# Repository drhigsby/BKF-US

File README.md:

# BKF Unibody Split (BKF-US)

A custom 40% unibody split keyboard PCB designed in KiCad.

## Overview

The BKF Unibody Split is a 4x12 (48-key) unibody split layout — both halves on a single PCB. It uses standard MX switches and is powered by an RP2040 Zero microcontroller.

## Layout

[KLE Preview](https://www.keyboard-layout-editor.com/#/gists/7dcf7c812452a509e0597ead96891f3b)

- 4x12 unibody split
- Standard MX switch footprints
- FR4 plate design included

## Hardware

- **MCU:** RP2040 Zero
- **Switches:** MX compatible
- **Plate:** FR4 (KiCad project included)

## Case

3D printable case files are included in the `case stuff/` directory:

- `bkf unibody split case v4.stl` — current case design
- `bkf unibody split case - extra planar cuts v1.stl` — variant with additional planar cuts
- `bkf unibody split case project.3mf` — OrcaSlicer project file with tuned slicing parameters
- `plate projected geometry only.dxf` — plate geometry for CAD reference
- `pcb test fit v1.stl` — PCB test fit model

## Firmware

VIAL firmware is available in the [drhigsby/vial-qmk](https://github.com/drhigsby/vial-qmk) fork under `keyboards/drhigsby/bkf_us/`.

## Project Structure

```
bkf-unibodysplit - primary pcb/   # Main PCB design
bkf-unibodysplit - plate design/  # FR4 plate design
case stuff/                        # Case STL files and DXFs
```

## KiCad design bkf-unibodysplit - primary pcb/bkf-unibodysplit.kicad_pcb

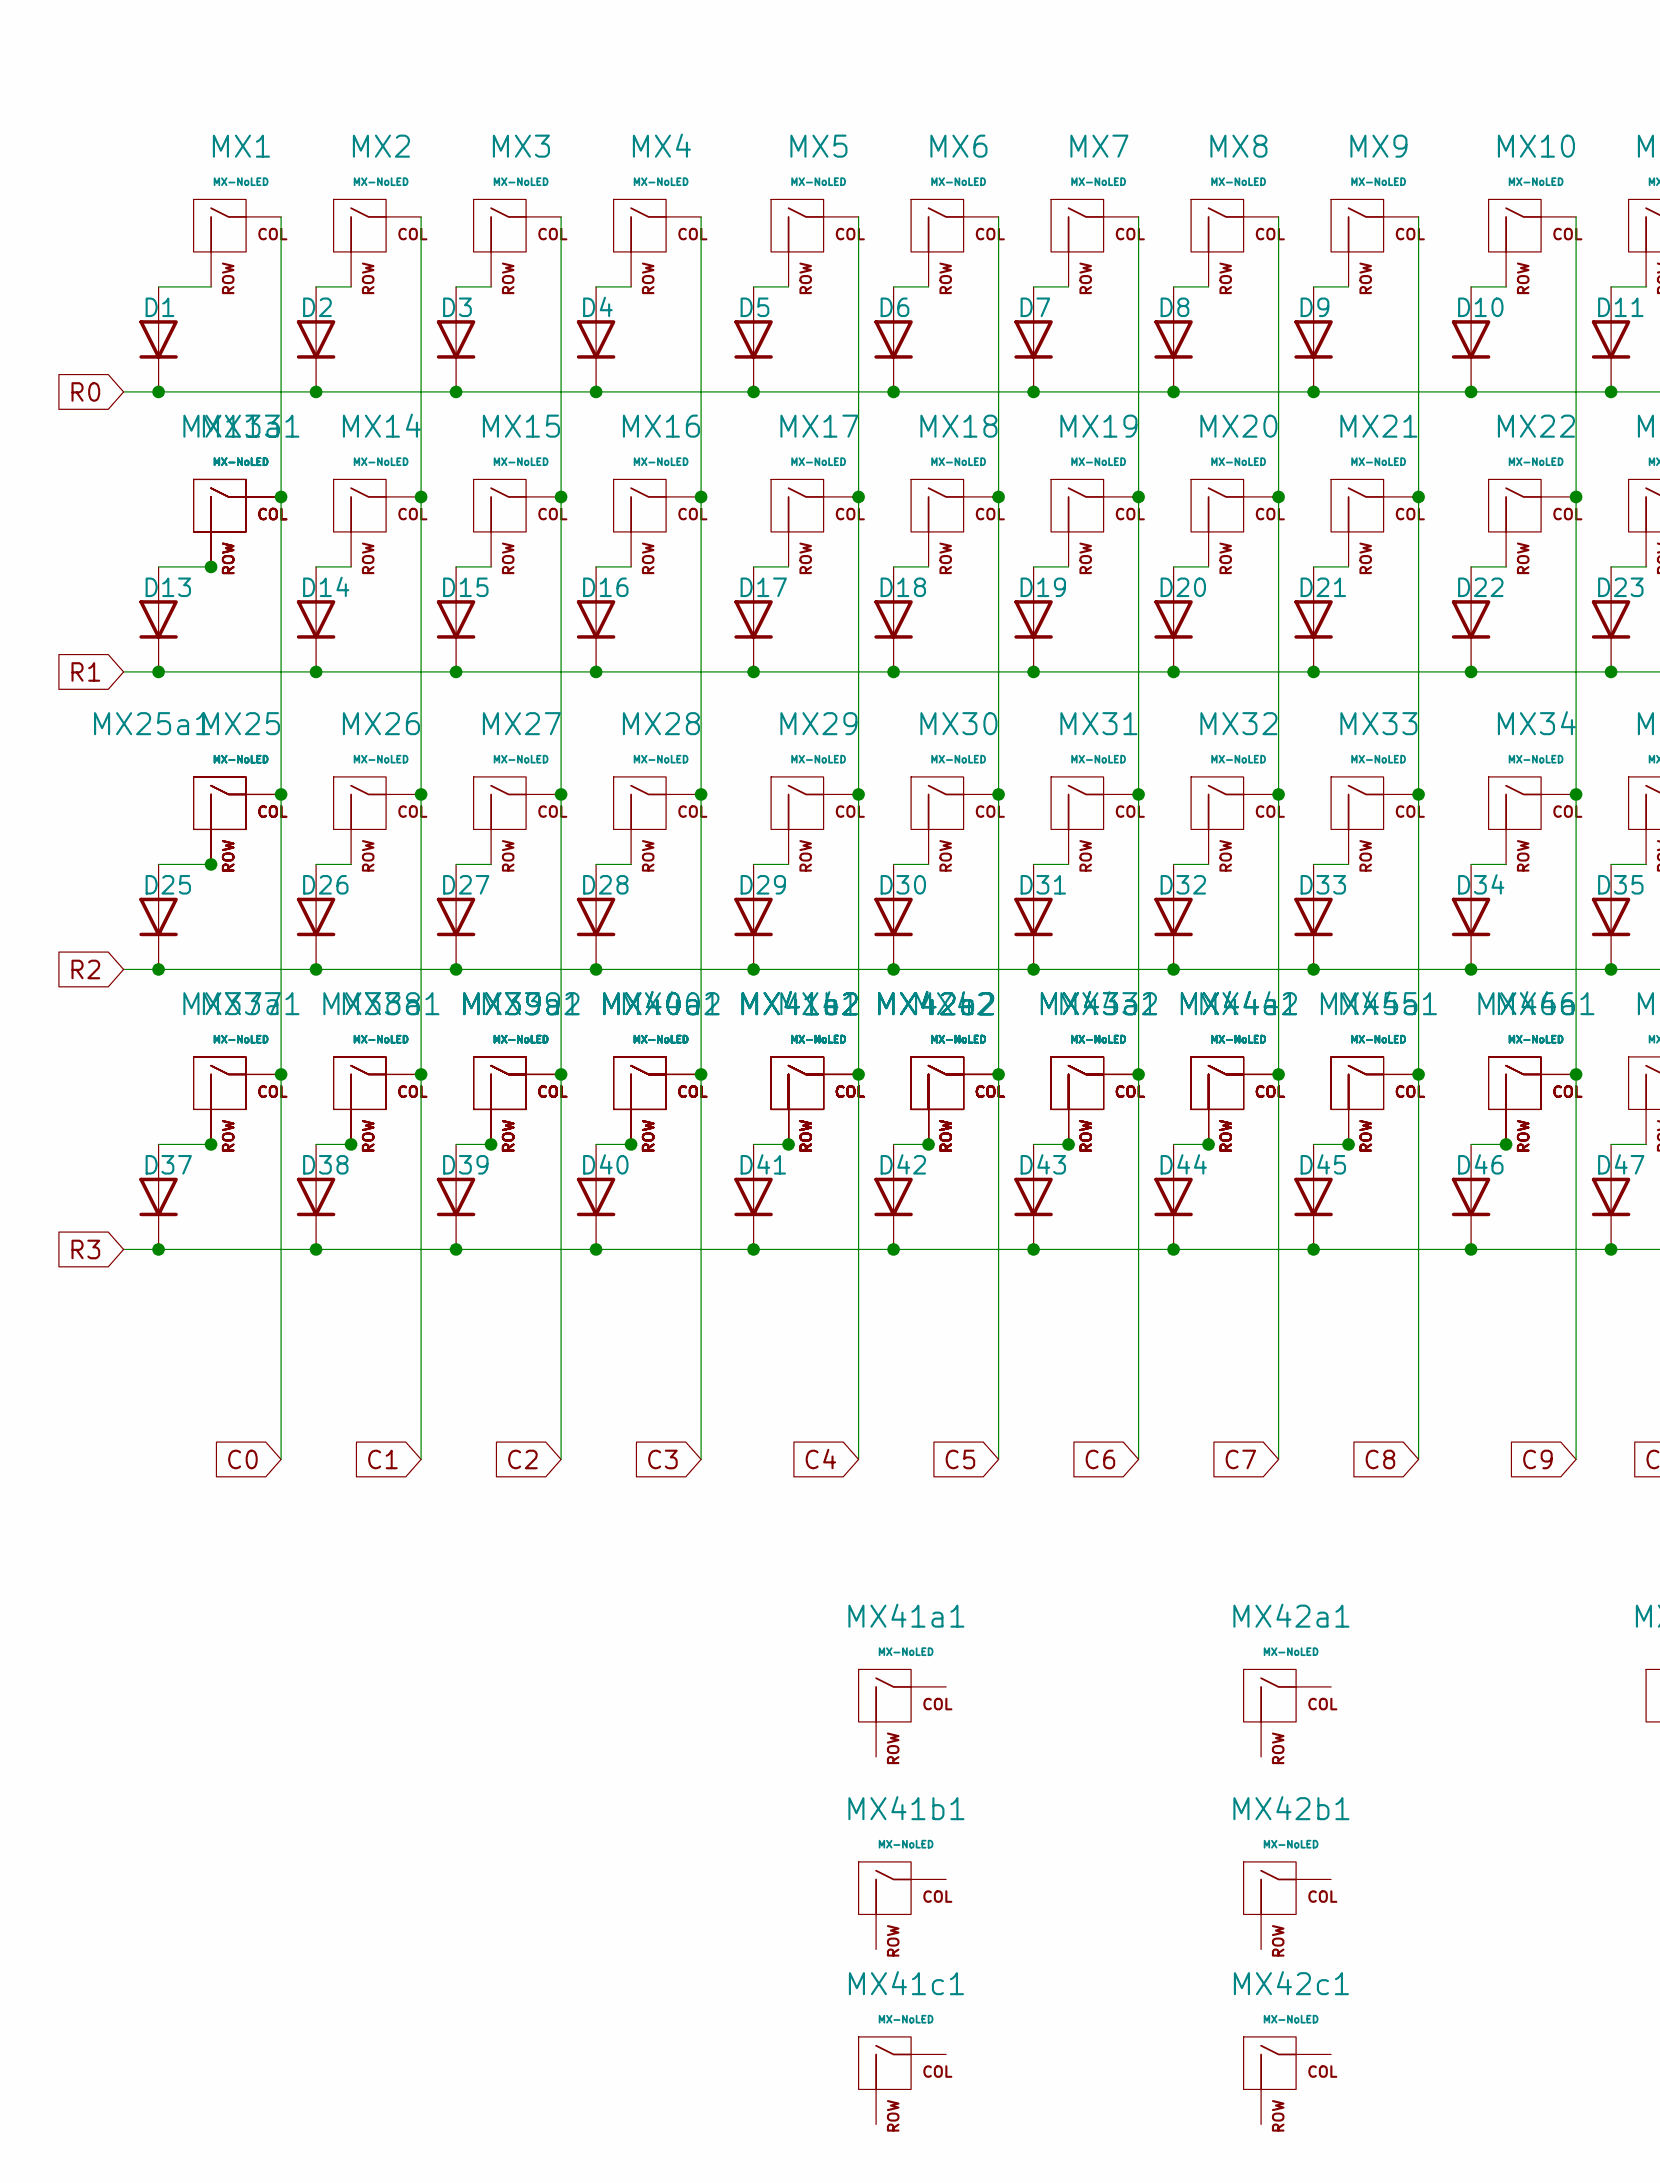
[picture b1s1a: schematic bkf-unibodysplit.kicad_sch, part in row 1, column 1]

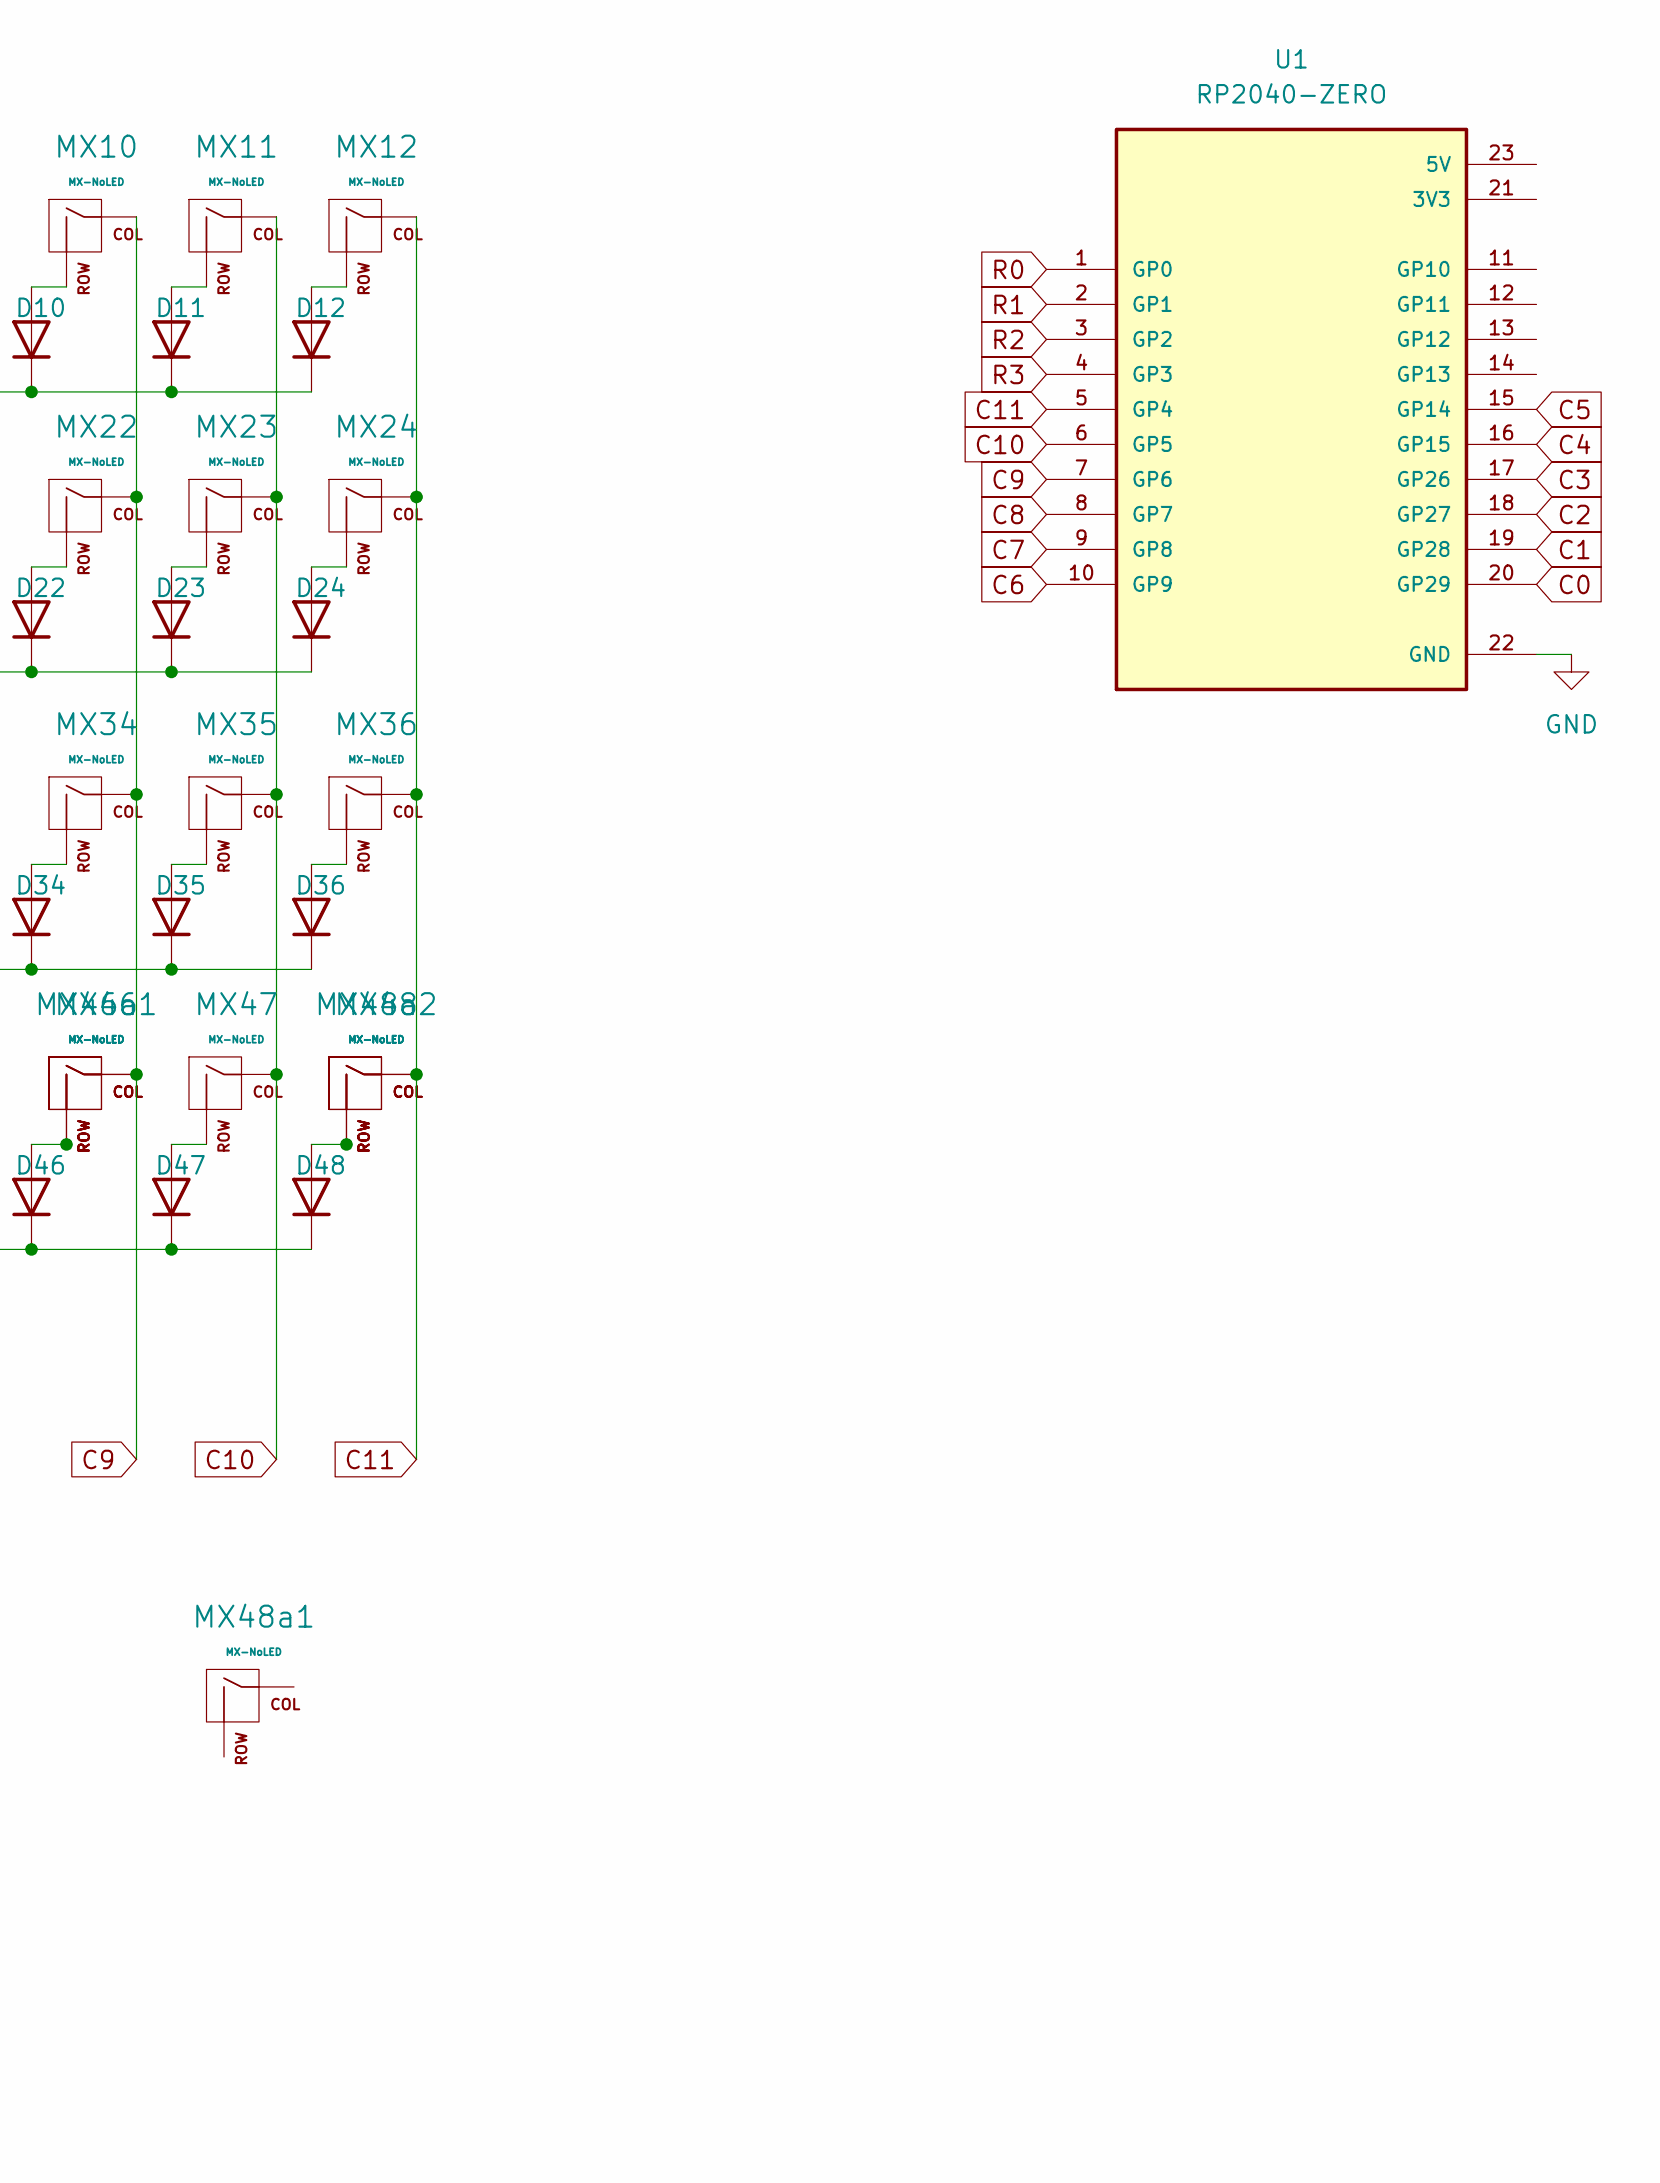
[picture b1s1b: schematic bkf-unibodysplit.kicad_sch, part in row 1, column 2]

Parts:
D1, D2, D3, D4, D5, D6, D7, D8, D9, D10, D11, D12, D13, D14, D15, D16, D17, D18, D19, D20, D21, D22, D23, D24, D25, D26, D27, D28, D29, D30, D31, D32, D33, D34, D35, D36, D37, D38, D39, D40, D41, D42, D43, D44, D45, D46, D47, D48: smt/tht hybrid; Diode-Hybrid-Back
MX1: MX-NoLED; SW_MX_1.5u
MX2, MX3, MX4, MX5, MX6, MX7, MX8, MX9, MX10, MX11, MX12, MX14, MX15, MX16, MX17, MX18, MX19, MX20, MX21, MX22, MX23, MX25a1, MX26, MX27, MX28, MX29, MX30, MX31, MX32, MX33, MX34, MX35, MX36, MX37a1, MX38, MX38a1, MX39, MX39a2, MX40a1, MX40a2, MX41a2, MX41b2, MX41c2, MX42a2, MX42b2, MX42c2, MX43a1, MX43a2, MX44, MX44a2, MX45, MX45a1, MX46a1, MX48, MX48a2: MX-NoLED; SW_MX_1u
MX13, MX24, MX41, MX42: MX-NoLED; SW_MX_1.75u
MX13a1: MX-NoLED; SW_MX_1.75u_stp
MX25, MX41b1, MX42b1: MX-NoLED; STAB_MX_P_2.25u
MX37, MX39a1, MX40, MX43, MX44a1, MX46, MX47: MX-NoLED; SW_MX_1.25u
MX41a1, MX42a1, MX48a1: MX-NoLED; STAB_MX_P_2u
MX41c1, MX42c1: MX-NoLED; STAB_MX_P_2.75u
U1: RP2040-ZERO; MODULE_RP2040-ZERO; PARTREV NA

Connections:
C0: MX1.1 (COL), MX13.1 (COL), MX13a1.1 (COL), MX25.1 (COL), MX25a1.1 (COL), MX37.1 (COL), MX37a1.1 (COL), U1.20 (GP29)
C1: MX2.1 (COL), MX14.1 (COL), MX26.1 (COL), MX38.1 (COL), MX38a1.1 (COL), U1.19 (GP28)
C2: MX3.1 (COL), MX15.1 (COL), MX27.1 (COL), MX39.1 (COL), MX39a1.1 (COL), MX39a2.1 (COL), U1.18 (GP27)
C3: MX4.1 (COL), MX16.1 (COL), MX28.1 (COL), MX40.1 (COL), MX40a1.1 (COL), MX40a2.1 (COL), U1.17 (GP26)
C4: MX5.1 (COL), MX17.1 (COL), MX29.1 (COL), MX41.1 (COL), MX41a2.1 (COL), MX41b2.1 (COL), MX41c2.1 (COL), U1.16 (GP15)
C5: MX6.1 (COL), MX18.1 (COL), MX30.1 (COL), MX42.1 (COL), MX42a2.1 (COL), MX42b2.1 (COL), MX42c2.1 (COL), U1.15 (GP14)
C6: MX7.1 (COL), MX19.1 (COL), MX31.1 (COL), MX43.1 (COL), MX43a1.1 (COL), MX43a2.1 (COL), U1.10 (GP9)
C7: MX8.1 (COL), MX20.1 (COL), MX32.1 (COL), MX44.1 (COL), MX44a1.1 (COL), MX44a2.1 (COL), U1.9 (GP8)
C8: MX9.1 (COL), MX21.1 (COL), MX33.1 (COL), MX45.1 (COL), MX45a1.1 (COL), U1.8 (GP7)
C9: MX10.1 (COL), MX22.1 (COL), MX34.1 (COL), MX46.1 (COL), MX46a1.1 (COL), U1.7 (GP6)
C10: MX11.1 (COL), MX23.1 (COL), MX35.1 (COL), MX47.1 (COL), U1.6 (GP5)
C11: MX12.1 (COL), MX24.1 (COL), MX36.1 (COL), MX48.1 (COL), MX48a2.1 (COL), U1.5 (GP4)
GND: U1.22 (GND)
unnamed: D1.2 (A), MX1.2 (ROW)
unnamed: D2.2 (A), MX2.2 (ROW)
unnamed: D3.2 (A), MX3.2 (ROW)
unnamed: D4.2 (A), MX4.2 (ROW)
unnamed: D5.2 (A), MX5.2 (ROW)
unnamed: D6.2 (A), MX6.2 (ROW)
unnamed: D7.2 (A), MX7.2 (ROW)
unnamed: D8.2 (A), MX8.2 (ROW)
unnamed: D9.2 (A), MX9.2 (ROW)
unnamed: D10.2 (A), MX10.2 (ROW)
unnamed: D11.2 (A), MX11.2 (ROW)
unnamed: D12.2 (A), MX12.2 (ROW)
unnamed: D13.2 (A), MX13.2 (ROW), MX13a1.2 (ROW)
unnamed: D14.2 (A), MX14.2 (ROW)
unnamed: D15.2 (A), MX15.2 (ROW)
unnamed: D16.2 (A), MX16.2 (ROW)
unnamed: D17.2 (A), MX17.2 (ROW)
unnamed: D18.2 (A), MX18.2 (ROW)
unnamed: D19.2 (A), MX19.2 (ROW)
unnamed: D20.2 (A), MX20.2 (ROW)
unnamed: D21.2 (A), MX21.2 (ROW)
unnamed: D22.2 (A), MX22.2 (ROW)
unnamed: D23.2 (A), MX23.2 (ROW)
unnamed: D24.2 (A), MX24.2 (ROW)
unnamed: D25.2 (A), MX25.2 (ROW), MX25a1.2 (ROW)
unnamed: D26.2 (A), MX26.2 (ROW)
unnamed: D27.2 (A), MX27.2 (ROW)
unnamed: D28.2 (A), MX28.2 (ROW)
unnamed: D29.2 (A), MX29.2 (ROW)
unnamed: D30.2 (A), MX30.2 (ROW)
unnamed: D31.2 (A), MX31.2 (ROW)
unnamed: D32.2 (A), MX32.2 (ROW)
unnamed: D33.2 (A), MX33.2 (ROW)
unnamed: D34.2 (A), MX34.2 (ROW)
unnamed: D35.2 (A), MX35.2 (ROW)
unnamed: D36.2 (A), MX36.2 (ROW)
unnamed: D37.2 (A), MX37.2 (ROW), MX37a1.2 (ROW)
unnamed: D38.2 (A), MX38.2 (ROW), MX38a1.2 (ROW)
unnamed: D39.2 (A), MX39.2 (ROW), MX39a1.2 (ROW), MX39a2.2 (ROW)
unnamed: D40.2 (A), MX40.2 (ROW), MX40a1.2 (ROW), MX40a2.2 (ROW)
unnamed: D41.2 (A), MX41.2 (ROW), MX41a2.2 (ROW), MX41b2.2 (ROW), MX41c2.2 (ROW)
unnamed: D42.2 (A), MX42.2 (ROW), MX42a2.2 (ROW), MX42b2.2 (ROW), MX42c2.2 (ROW)
unnamed: D43.2 (A), MX43.2 (ROW), MX43a1.2 (ROW), MX43a2.2 (ROW)
unnamed: D44.2 (A), MX44.2 (ROW), MX44a1.2 (ROW), MX44a2.2 (ROW)
unnamed: D45.2 (A), MX45.2 (ROW), MX45a1.2 (ROW)
unnamed: D46.2 (A), MX46.2 (ROW), MX46a1.2 (ROW)
unnamed: D47.2 (A), MX47.2 (ROW)
unnamed: D48.2 (A), MX48.2 (ROW), MX48a2.2 (ROW)
R0: D1.1 (K), D2.1 (K), D3.1 (K), D4.1 (K), D5.1 (K), D6.1 (K), D7.1 (K), D8.1 (K), D9.1 (K), D10.1 (K), D11.1 (K), D12.1 (K), U1.1 (GP0)
R1: D13.1 (K), D14.1 (K), D15.1 (K), D16.1 (K), D17.1 (K), D18.1 (K), D19.1 (K), D20.1 (K), D21.1 (K), D22.1 (K), D23.1 (K), D24.1 (K), U1.2 (GP1)
R2: D25.1 (K), D26.1 (K), D27.1 (K), D28.1 (K), D29.1 (K), D30.1 (K), D31.1 (K), D32.1 (K), D33.1 (K), D34.1 (K), D35.1 (K), D36.1 (K), U1.3 (GP2)
R3: D37.1 (K), D38.1 (K), D39.1 (K), D40.1 (K), D41.1 (K), D42.1 (K), D43.1 (K), D44.1 (K), D45.1 (K), D46.1 (K), D47.1 (K), D48.1 (K), U1.4 (GP3)

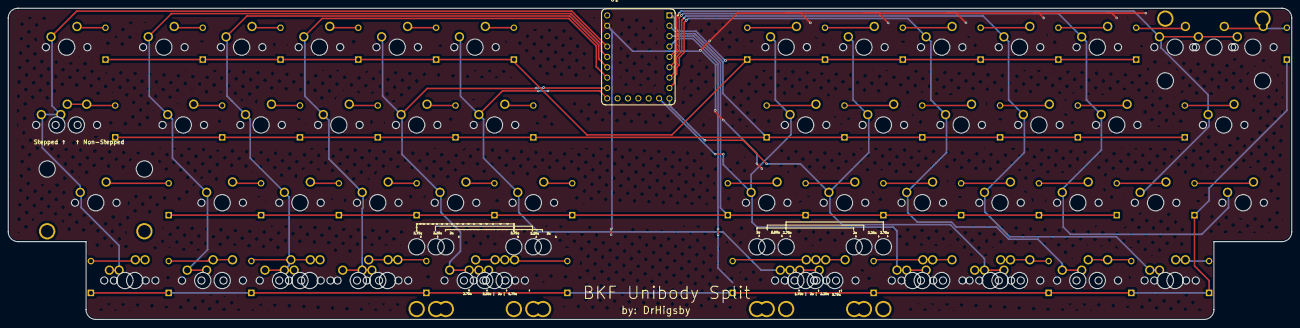
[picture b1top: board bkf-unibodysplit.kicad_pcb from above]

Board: 2 copper layers, 314.3 x 76.2 mm, 125 parts (0 on the bottom side), 64 nets.

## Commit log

2026-06-09 Initial commit: BKF Unibody Split KiCad PCB, plate, and case files
2026-06-09 Add README, update gitignore, remove outdated case file versions
